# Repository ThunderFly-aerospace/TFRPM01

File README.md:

# TFRPM01 - RPM Measuring UAV Avionics Device

## Overview
The TFRPM is designed to measure revolutions per minute (RPM) in UAVs. It connects directly to Pixhawk controllers like CUAV V5+ or Holybro Pixhawk 6X via a [standard I²C connector](https://github.com/pixhawk/Pixhawk-Standards/blob/master/DS-009%20Pixhawk%20Connector%20Standard.pdf) and has the driver in PX4 firmware.

## Specifications

### Features
- **Schmitt Trigger Input**: To shape non-uniform signals from RPM sensing elements.
- **Self-Counting and Memory**: Offloads the flight controller's MCU.
- **LED Indicator**: Optionally visible in daylight for input status.
- **Protection**: Short-circuit protection on the probe connector.
- **I²C Connectors**: Pass-through connectors for daisy-chaining sensors.
- **Design**: Robust and repairable.

### Technical Parameters
- **Pulse Frequency Range**: 0 - 20 kHz.
- **I2C Connector**: 2x 4-pin JST-GH.
- **RPM Connector**: 3-pin 2.54mm pitch header.
- **I2C Address**: 0x50 default, alterable to 0x51.
- **Operating Temperature**: −20°C to +40°C.
- **Input Voltage**: +3.6V to +5.4V.
- **Mass**: 12g (4g PCB + 8g case).
- **Dimensions**: Case - 23.5x42x12.5mm, PCB - 37.5x19mm.
- **Weather Resistance**: IP40.

### Where to Get It?
TFRPM can be bought directly from ThunderFly via [email contact](https://www.thunderfly.cz/contact-us.html). The email can also be used if there are specific requirements for custom modifications or if the product will be inquired in significant quantities. TFRPM is also available for online purchase through the [Tindie store](https://www.tindie.com/products/thunderfly/tfrpm01-drone-rpm-tachometer-sensor/).

### Connection to Pixhawk Autopilot
Follows the [Pixhawk connector standard](https://github.com/pixhawk/Pixhawk-Standards/blob/master/DS-009%20Pixhawk%20Connector%20Standard.pdf) with specific color coding.

### I²C Address Configuration
The default address is 0x50, changeable to 0x51.

### Mounting Options
The device can be mounted with or without a provided 3D-printed case.

### Sensor Probe Selection

Compatible with multiple probe types, including Hall effect and optical probes. See the [TFPROBE01](https://github.com/ThunderFly-aerospace/TFPROBE01) and [TFRPM01 documentation](https://docs.thunderfly.cz/avionics/TFRPM01/) for details.

Third-party hall probe sensors could also be used; here is an example of a suitable generic hall probe with a mounting flange.

## Software Configuration

Supported by PX4 firmware. Setup instructions are available in the [PX4 documentation](https://docs.px4.io/main/en/sensor/thunderfly_tachometer.html#software-setup).

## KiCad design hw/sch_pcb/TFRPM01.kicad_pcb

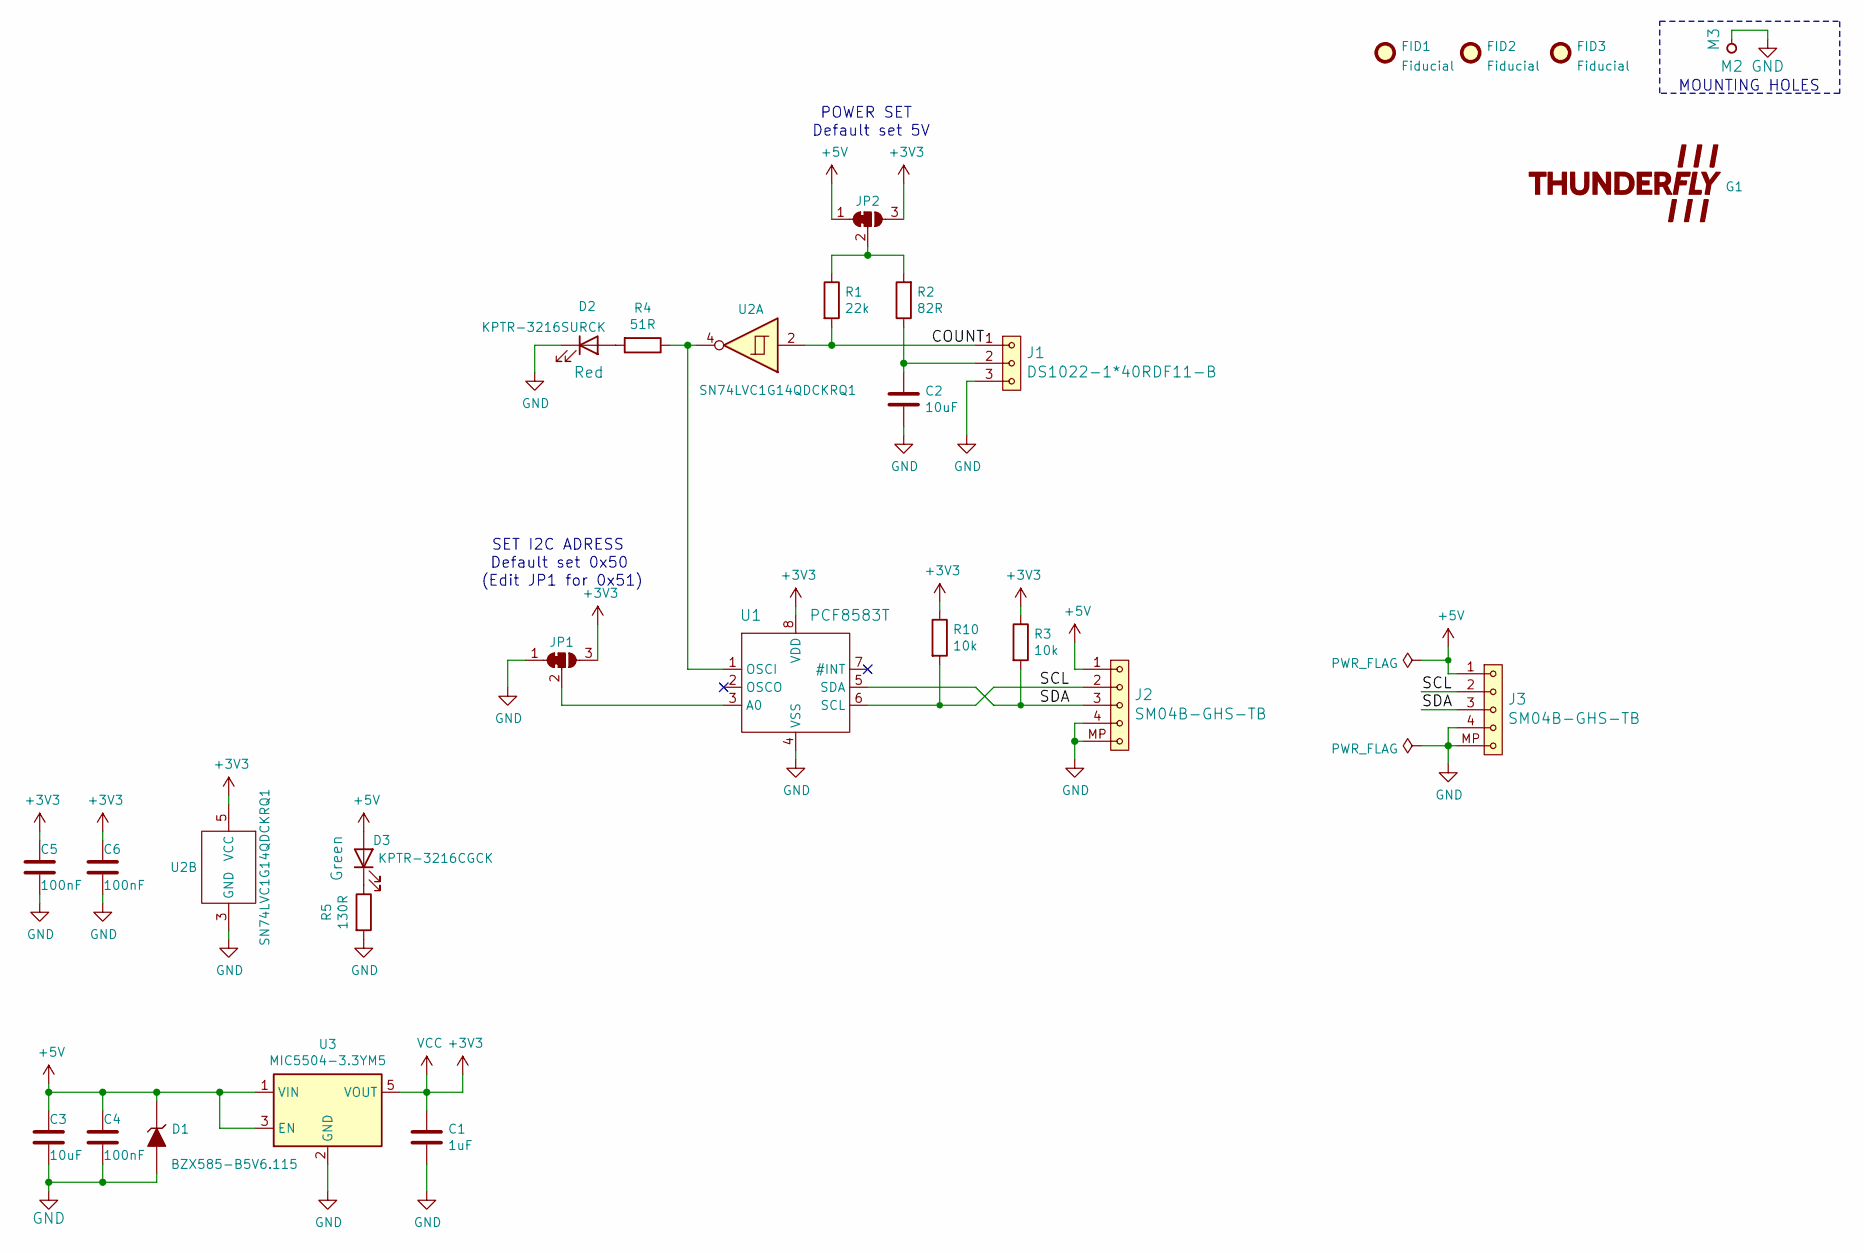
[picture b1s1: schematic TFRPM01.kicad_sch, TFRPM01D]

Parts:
C1: 1uF; C_0603_1608Metric
C2, C3: 10uF; C_0603_1608Metric
C4, C5, C6: 100nF; C_0603_1608Metric
D1: BZX585-B5V6.115; D_SOD-523
D2: KPTR-3216SURCK; LED_1206_2
D3: KPTR-3216CGCK; LED_1206_2
FID1, FID2, FID3: Fiducial; Fiducial_0.5mm_Mask1.5mm
G1: LOGO; TF
J1: DS1022-1*40RDF11-B; PinHeader_1x03_P2.54mm_Horizontal
J2, J3: SM04B-GHS-TB; JST_GH_SM04B-GHS-TB_1x04-1MP_P1.25mm_Horizontal
JP1, JP2: SolderJumper_3_Bridged12; SolderJumper-3_P1.3mm_Bridged12_RoundedPad1.0x1.5mm
M2: M3; MountingHole_3mm
R1: 22k; R_0805_2012Metric
R2: 82R; R_0805_2012Metric
R3, R10: 10k; R_0603_1608Metric
R4: 51R; R_0603_1608Metric
R5: 130R; R_0603_1608Metric
U1: PCF8583T; SOT176-1
U2: SN74LVC1G14QDCKRQ1; SOT-353_SC-70-5
U3: MIC5504-3.3YM5; SOT-23-5

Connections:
+3V3: C1.1, C5.1, C6.1, JP1.3 (B), JP2.3 (B), R3.1, R10.1, U1.8 (VDD), U2.5 (VCC), U3.5 (VOUT)
+5V: C3.1, C4.1, D1.1 (K), D3.2 (A), J2.1, J3.1, JP2.1 (A), U3.1 (VIN), U3.3 (EN)
/COUNT: J1.1, R1.2, U2.2
/SCL: J2.2, J3.2, R10.2, U1.6 (SCL)
/SDA: J2.3, J3.3, R3.2, U1.5 (SDA)
GND: C1.2, C2.2, C3.2, C4.2, C5.2, C6.2, D1.2 (A), D2.1 (K), J1.3, J2.4, J2.MP, J3.4, J3.MP, JP1.1 (A), M2.1, R5.2, U1.4 (VSS), U2.3 (GND), U3.2 (GND)
unnamed: C2.1, J1.2, R2.1
unnamed: D2.2 (A), R4.2
unnamed: D3.1 (K), R5.1
unnamed: JP1.2 (C), U1.3 (A0)
unnamed: JP2.2 (C), R1.1, R2.2
unnamed: R4.1, U1.1 (OSCI), U2.4

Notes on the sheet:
Default set 5V
(Edit JP1 for 0x51)
MOUNTING HOLES
Default set 0x50
POWER SET
SET I2C ADRESS

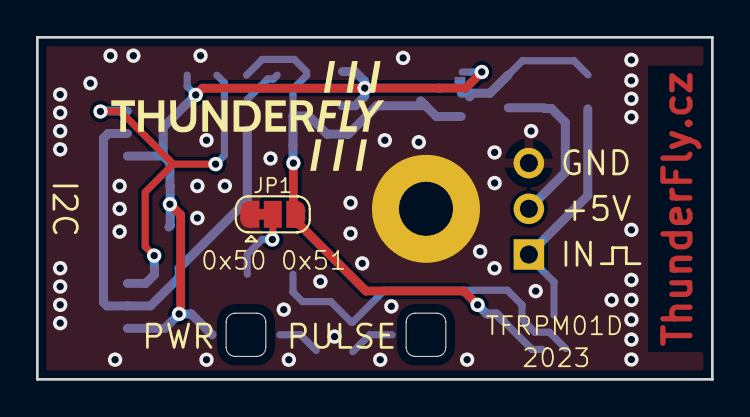
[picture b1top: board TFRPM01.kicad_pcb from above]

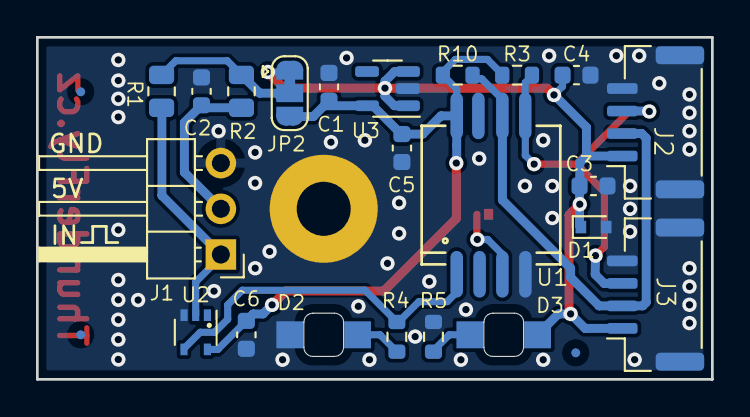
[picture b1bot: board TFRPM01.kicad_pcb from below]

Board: 2 copper layers, 37.5 x 19.0 mm, 28 parts (26 on the bottom side), 12 nets.

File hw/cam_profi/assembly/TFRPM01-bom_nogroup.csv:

Component,Description,Part,References,Value,Footprint,Quantity Per PCB,Datasheet,ust_id,color
1,Unpolarized capacitor,C,C4C5C6,100nF,C_0603_1608Metric,3,~,5c70984812875079b91f8bf2,
2,Unpolarized capacitor,C,C1,1uF,C_0603_1608Metric,1,~,5c70984812875079b91f8bc2,
3,Unpolarized capacitor,C,C2C3,10uF,C_0603_1608Metric,2,~,5c70984812875079b91f8bf5,
4,,D_ZENER,D1,BZX585-B5V6.115,D_SOD-523,1,,60879d38128750769ee58e48,
5,Light emitting diode,LED,D3,KPTR-3216CGCK,LED_1206_2,1,~,,Green
6,Light emitting diode,LED,D2,KPTR-3216SURCK,LED_1206_2,1,~,,Red
7,1x03 2.54 mm pitch header,HEADER_1x03,J1,DS1022-1*40RDF11-B,PinHeader_1x03_P2.54mm_Horizontal,1,5c70984412875079b91f879d,,
8,,SM04B-GHS-TB_1,J2,SM04B-GHS-TB,JST_GH_SM04B-GHS-TB_1x04-1MP_P1.25mm_Horizontal,1,,5c86273d1287500b4e0280be,
9,,SM04B-GHS-TB,J3,SM04B-GHS-TB,JST_GH_SM04B-GHS-TB_1x04-1MP_P1.25mm_Horizontal,1,,5c86273d1287500b4e0280be,
10,Resistor,R,R4,51R,R_0603_1608Metric,1,~,5c70984512875079b91f8953,
11,Resistor,R,R2,82R,R_0805_2012Metric,1,~,5c70984512875079b91f8976,
12,Resistor,R,R5,130R,R_0603_1608Metric,1,~,5cd08b17128750448e4542b1,
13,Resistor,R,R3R10,10k,R_0603_1608Metric,2,~,5c70984512875079b91f8962,
14,Resistor,R,R1,22k,R_0805_2012Metric,1,~,5c70984712875079b91f8a87,
15,"300mA Low-dropout Voltage Regulator, Vout 3.3V, Vin up to 5.5V, SOT-23",MIC5504-3.3YM5,U3,MIC5504-3.3YM5,SOT-23-5,1,http://ww1.microchip.com/downloads/en/DeviceDoc/MIC550X.pdf,5c7255e81287500b4e112ea2,
16,,PCF8583,U1,PCF8583T,SOT176-1,1,https://www.nxp.com/docs/en/data-sheet/PCF8583.pdf,5c70984712875079b91f8b59,
17,Hex inverter schmitt trigger,74AHC1G14GV,U2,SN74LVC1G14QDCKRQ1,SOT-353_SC-70-5,1,http://www.ti.com/lit/gpn/sn74HC14,604b05e1128750769e5b106e,

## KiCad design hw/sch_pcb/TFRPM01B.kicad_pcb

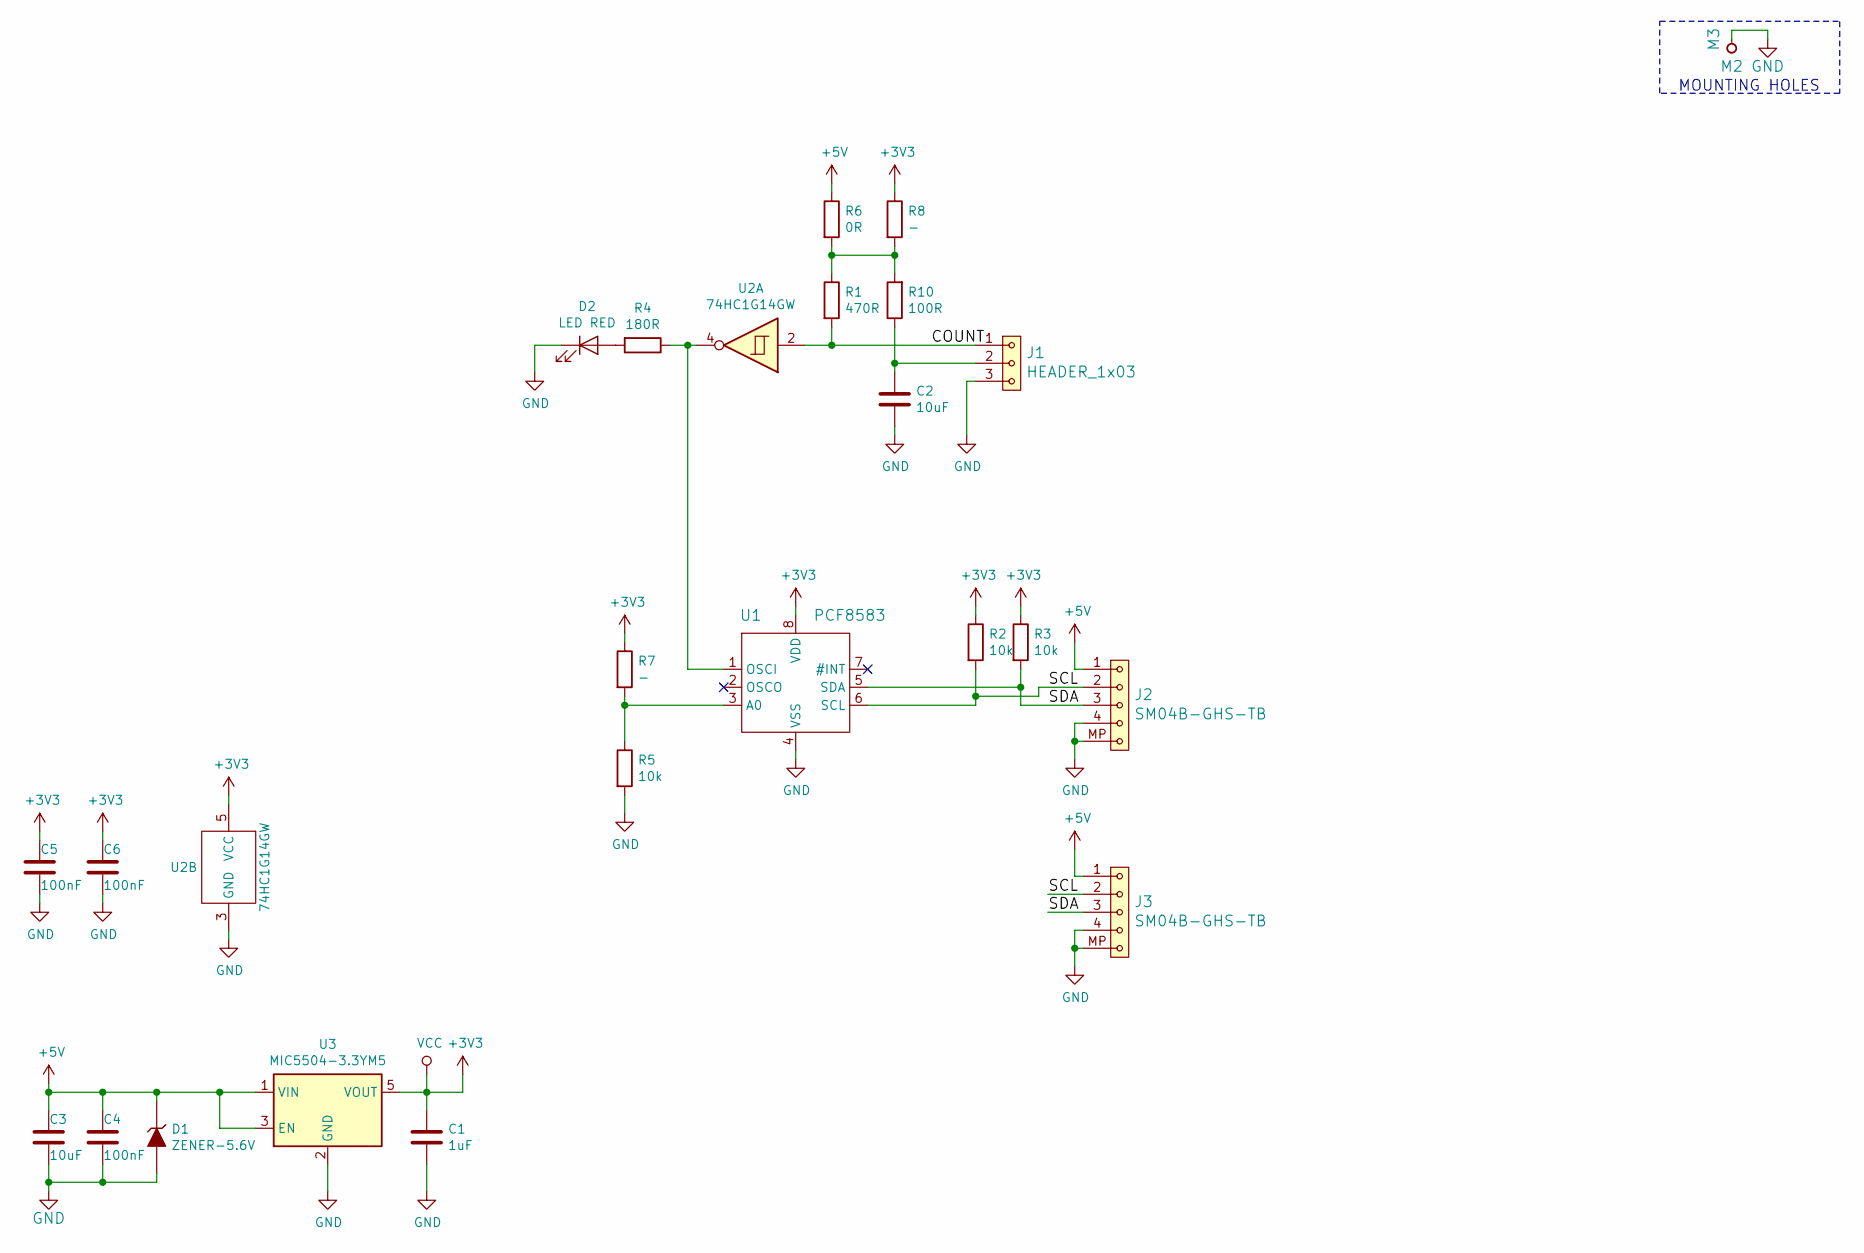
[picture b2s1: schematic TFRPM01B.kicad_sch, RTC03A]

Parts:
C1: 1uF; SMD-0603
C2, C3: 10uF; SMD-0805
C4, C5, C6: 100nF; SMD-0603
D1: ZENER-5.6V; Diode-MiniMELF_Standard
D2: LED RED; LED_1206
J1: HEADER_1x03; PinHeader_1x03_P2.54mm_Horizontal
J2, J3: SM04B-GHS-TB; JST_GH_SM04B-GHS-TB_1x04-1MP_P1.25mm_Horizontal
M2: M3; MountingHole_3mm
R1: 470R; SMD-0603
R2, R3, R5: 10k; SMD-0603
R4: 180R; SMD-0603
R6: 0R; SMD-0603
R7, R8: -; SMD-0603
R10: 100R; SMD-0603
U1: PCF8583; SOT176-1
U2: 74HC1G14GW; SOT-353_SC-70-5
U3: MIC5504-3.3YM5; SOT-23-5

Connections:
+3V3: C1.1, C5.1, C6.1, R2.1, R3.1, R7.1, R8.1, U1.8 (VDD), U2.5 (VCC), U3.5 (VOUT)
+5V: C3.1, C4.1, D1.1 (K), J2.1, J3.1, R6.1, U3.1 (VIN), U3.3 (EN)
/COUNT: J1.1, R1.2, U2.2
/SCL: J2.2, J3.2, R2.2, U1.6 (SCL)
/SDA: J2.3, J3.3, R3.2, U1.5 (SDA)
GND: C1.2, C2.2, C3.2, C4.2, C5.2, C6.2, D1.2 (A), D2.1 (K), J1.3, J2.4, J2.MP, J3.4, J3.MP, M2.1, R5.2, U1.4 (VSS), U2.3 (GND), U3.2 (GND)
unnamed: C2.1, J1.2, R10.1
unnamed: D2.2 (A), R4.2
unnamed: R1.1, R6.2, R8.2, R10.2
unnamed: R4.1, U1.1 (OSCI), U2.4
unnamed: R5.1, R7.2, U1.3 (A0)

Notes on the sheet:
MOUNTING HOLES

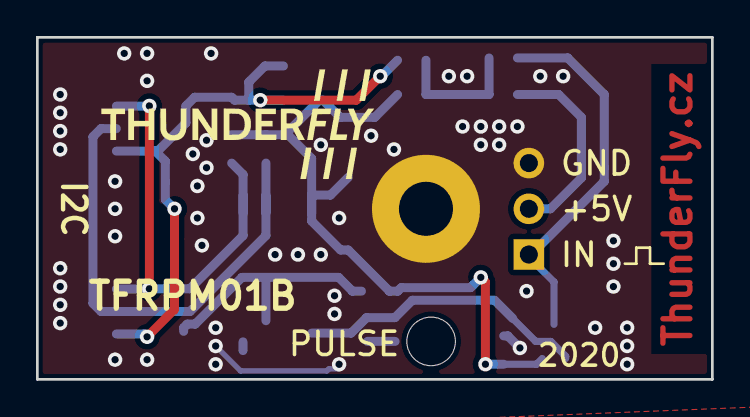
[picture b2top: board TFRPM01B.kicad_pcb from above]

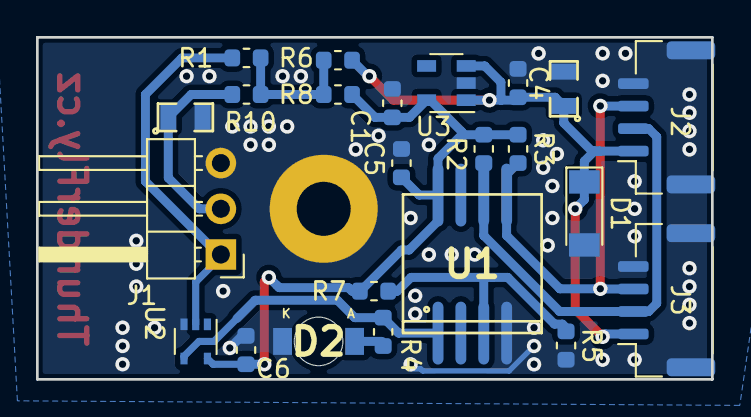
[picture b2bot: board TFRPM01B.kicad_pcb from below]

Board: 2 copper layers, 37.5 x 19.0 mm, 24 parts (24 on the bottom side), 11 nets.

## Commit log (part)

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2022-03-15 Update submodule to latest
2022-03-16 vycisteni repozitare, prejmenovani na verzi D
2022-03-16 aktualizace actions
2022-03-16 add workflow
2022-03-16 Upraveni PCB, pridani popisku, vyresení #21, #26, urava silkscreenu, vypocet polohy led v openscadu
2022-03-16 Push actions product
2022-03-29 update action, clean repo
2022-03-29 procisteni dat
2022-03-30 update assets
2022-03-30 Update actions products
2022-04-04 zrcadleni vystupu
2022-04-04 drc filter
2022-07-20 LED case bug fix
2022-09-19 Výměna pouzder LED a D zener
2022-09-26 Edit PCB. LED footprint. 10uF 0805 to 0603
2022-09-26 Edit
2022-09-28 Graphics and layout improvements. Net classes for default and power set.
2022-09-29 Repair #30
2022-09-30 Silkscreen modification
2022-10-03 Improve silkscreen.
2022-10-03 Improve layout uniform track widts. Resolve DRC and ERC issues.
2022-10-03 silkscreen improvement.
2022-10-03 Move JP1 far away from TF logo.
2022-10-03 Move trace to avoid sharp angles.
2022-10-03 reduced thickness of text.
2022-10-18 Edit PCB
2022-11-11 Explain measurement resolution.
2022-11-11 Fix equation clarity.
2022-11-11 check spelling.
2023-01-21 Edit BOM
2023-01-21 Edit B.FAB
2023-02-11 Update README.md
    spell check.
2023-02-24 Update README.md
    Add the link to oshwa certification.
2023-03-05 update case for 01D
2023-03-15 sticker
2023-03-15 podtisk, nahledove pdf
2023-03-17 Vyrobni data
2023-03-19 add preview, test page
2023-03-29 uprava pretisku
2023-04-23 Restore previous workflow.
2023-04-23 Update github actions.
2023-05-05 Update nut dimensions and tolerances
2023-05-06 Modify workflow to take specific KiCAD project name.
2023-05-07 update actions
2023-05-07 rename kicad files
2023-05-07 Clean some dust from images.
2023-05-07 Update PCB dimensions image.
2023-05-17 resave project file
2023-05-17 Uprava atributu U1
2023-05-22 Fix metadata updater workflow issue.
2023-05-22 Update metadata_updater.yml
    Removing kitspace metadata update
2023-05-26 Exclude Fiducial + SolderJumper_3_Bridged12 + M3 from BOM.
2023-05-26 Update part number marking.
2023-05-26 Update Rev.
2023-05-26 Upgrade PCB from schematics. Minor layout improvement of sharp track in case of LED and U2 pads.
2023-05-27 Update workflow files
2023-05-27 aktualizace assets
2023-05-27 Update metadata files
2023-05-31 try to remove holes support
2023-05-31 Add gcodes
2023-06-01 Change type marking of pin_header.
2023-06-01 Upgrade PCB from schematics.
2023-06-05 DRC check.
2023-06-07 Remove unecessary kitspace file.
2023-06-13 Update LEDs part numbers.
2023-06-14 Updated year mark in silkscreen.
2023-07-31 Update README.md
    Readme spell check.
2023-07-31 Update README.md
    Add information on support ICE RPM measurement.
2023-07-31 Update README.md
    Improve contact link.
2023-07-31 Update tindie.md
    Synchronise with Tindie listing.
2023-07-31 Update tindie.md
    Spell check.
2023-07-31 Update tindie.md
    Reformulate introducing sentences.
2023-09-12 Update README.md
    Sort Features list.
2024-02-08 new interactive QC tool
2024-02-08 Change beep logic.
2024-02-08 Improve documentation add valid test result.
2024-02-13 Update tindie.md
    update from tindie.
2024-02-13 Update tindie.md
    Update changelog. (Roll-back to screw hole)
2024-03-08 Update README.md
    Simplifying readme.
2024-03-10 Remove unused file.
2024-05-02 Update KiCAD project. Add spreadsheet to calculate voltage tresholds.
2024-05-30 Cleanup schematics.
2024-05-30 Switch project to KiCad7
2024-05-30 Update workflows to KiCAD7.
2024-05-30 Update schematics symbols and PCBs to resolve errors in action run.
2024-05-30 Remove permanent selection of assets branch.
2024-10-18 Update README.md
    Improve documentation.
2024-11-01 Update testing script. Attempt to fix new python3 dependencies.
2024-11-02 Removing unecessary comments.
2024-11-04 Add datasheet to hall probe sensor with flange.
2024-11-07 Replaced the beepy library with a generated sound and sounddevice lib.
2024-11-07 Modify code to stay in curses even in case of error.
2024-11-07 Adding HID permissions testing script.
2025-07-02 Imrove cabling section.
2025-07-02 Improve links and texts.
